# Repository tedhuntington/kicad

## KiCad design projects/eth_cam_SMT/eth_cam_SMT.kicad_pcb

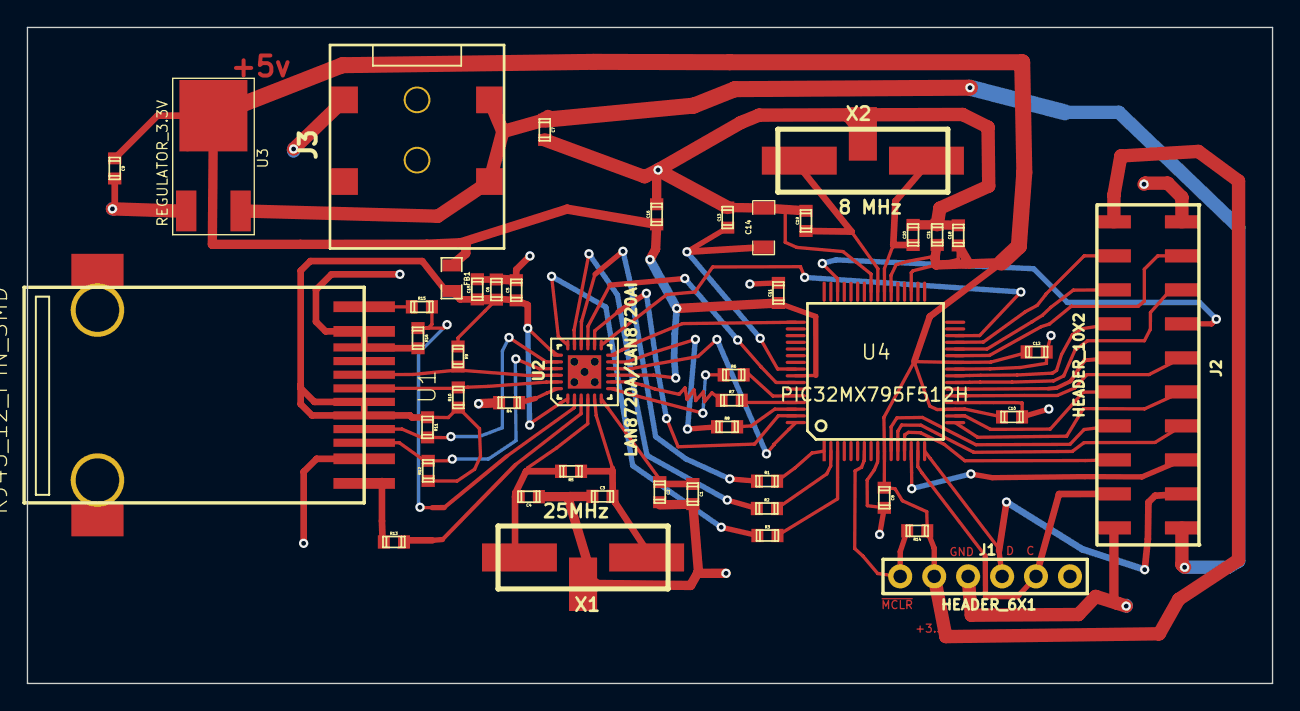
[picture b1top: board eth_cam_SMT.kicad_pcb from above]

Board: 2 copper layers, 93.0 x 49.0 mm, 46 parts (0 on the bottom side), 53 nets.

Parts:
C1, C5, C6, C8, C10, C11, C12, C13, C16, C18, C21: .1uF; TED_SM0603
C2, C15: 1uF; TED_SM0603
C3, C4, C19, C20: 18pF; TED_SM0603
C7, C9: 4.7uF; TED_SM0603
C14: 10uF; TED_SM1206
FB1: 500mA; TED_SM0805
J1: HEADER_6X1; TED_HEADER_6x1_BOTTOM
J2: HEADER_10X2; TED_HEADER_10x2_SMT
J3: Logic DC_2.1MM; TED_DC_2.1mm_SMT
R1, R2, R3, R6, R7, R8: 33; TED_SM0603
R4: 12.1k 1%; TED_SM0603
R5: 1M; TED_SM0603
R9, R10, R11, R12: 49.9; TED_SM0603
R13, R15: 249; TED_SM0603
R14: 4.7k; TED_SM0603
R16: 10k 1%; TED_SM0603
U1: RJ45_12_PIN_SMD; TED_RJ45_12pin_SMD
U2: LAN8720A/LAN8720AI; TED_QFN24
U3: REGULATOR_3.3V; TED_3v_DPAK
U4: PIC32MX795F512H; TQFP_64
X1: 25MHz; TED_crystal_W_GND_SMT_13x5mm
X2: 8 MHz; TED_crystal_W_GND_SMT_13x5mm

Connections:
+3.3v: C8.1, C9.1, C10.1, C11.1, C12.1, C16.1, C18.1, C21.1, FB1.1, J1.2, J2.11, R14.1, U2.9, U3.2, U4.10, U4.19, U4.26, U4.35, U4.38, U4.57
+5v: C7.1, J2.1, J3.1, U3.3
AVDD: C5.1, C6.1, C15.1, FB1.2, R9.1, R10.1, R11.1, R12.1, U1.5, U1.6, U2.1, U2.19
ECRSDV: R8.2, U4.62
EMDC: U2.13, U4.30
EMDIO: U2.12, U4.49
EREFCLK: U2.14, U4.63
ERXD0: R7.2, U4.61
ERXD1: R6.2, U4.60
ERXERR: U2.10, U4.64
ETXD0: R2.2, U4.2
ETXD1: R3.2, U4.3
ETXEN: R1.2, U4.1
GND: C1.2, C2.2, C3.1, C4.1, C5.2, C6.2, C7.2, C8.2, C9.2, C10.2, C11.2, C12.2, C13.2, C14.2, C15.2, C16.2, C18.2, C19.2, C20.2, C21.2, J1.3, J2.10, J2.20, J3.2, R4.2, R16.2, U1.2, U1.10, U1.11, U2.25, U3.1, U4.9, U4.20, U4.25, U4.41, X1.3, X2.3
GreenLED: R15.1, U1.12
ICSPCLK_RB1: J1.5, J2.19, U4.15
ICSPDAT_RB0: J1.4, J2.2, U4.16
unnamed: R7.1, U2.8
unnamed: R6.1, U2.7
unnamed: R4.1, U2.24
unnamed: R13.2, U2.3
unnamed: R15.2, R16.1, U2.2
unnamed: C19.1, U4.40, X2.1
unnamed: R1.1, U2.16
unnamed: R2.1, U2.17
unnamed: R3.1, U2.18
unnamed: C4.2, R5.2, U2.4, X1.2
unnamed: C3.2, R5.1, U2.5, X1.1
unnamed: C1.1, C2.1, U2.6
unnamed: R8.1, U2.11
unnamed: C13.1, C14.1, U4.56
unnamed: C20.1, U4.39, X2.2
RB2: J2.3, U4.14
RB3: J2.18, U4.13
RB4: J2.4, U4.12
RB5: J2.17, U4.11
RB6: J2.5, U4.17
RB7: J2.16, U4.18
RB8: J2.6, U4.21
RB9: J2.15, U4.22
RB10: J2.8, U4.23
RB11: J2.14, U4.24
RB12: J2.9, U4.27
RB13: J2.13, U4.28
RB14: J2.12, U4.29
RD0: J2.7, U4.46
RXN: R9.2, U1.8, U2.22
RXP: R10.2, U1.7, U2.23
TXN: R11.2, U1.4, U2.20
TXP: R12.2, U1.3, U2.21
YellowLED: R13.1, U1.1
nRST: U2.15, U4.58
~MCLR~: J1.1, R14.2, U4.7

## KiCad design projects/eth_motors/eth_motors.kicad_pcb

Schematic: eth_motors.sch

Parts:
C1, C6, C16: .1uF
C2, C15: 1uF
C3, C4: 18pF
C7, C9: 4.7uF
FB1: 500mA
H1, H2, H3, H4: HOLE
J1: HEADER_6X1
J3: Logic DC_2.1MM; TED_DC_2.1mm
R1, R2, R3, R6, R7, R8: 33
R4: 12.1k 1%
R5: 1M
R9, R10, R11, R12: 49.9
R13, R15: 249
R16: 10k 1%
U1: RJ45_12_PIN_SMD
U2: LAN8720A/LAN8720AI; QFN24
U3: REGULATOR
X1: 25MHz

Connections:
+2.8v: C9.1, C16.1, FB1.1, J1.2, U2.9, U3.2; also elsewhere on the board
+5v: C7.1, J3.1, U3.3
AECRSDV: R8.2; also elsewhere on the board
AEMDC: U2.13; also elsewhere on the board
AEMDIO: U2.12; also elsewhere on the board
AEREFCLK: U2.14; also elsewhere on the board
AERXD0: R7.2; also elsewhere on the board
AERXD1: R6.2; also elsewhere on the board
AERXERR: U2.10; also elsewhere on the board
AETXD0: R2.2; also elsewhere on the board
AETXD1: R3.2; also elsewhere on the board
AETXEN: R1.2; also elsewhere on the board
AVDD: C6.1, C15.1, FB1.2, R9.1, R10.1, R11.1, R12.1, U1.5 (CT), U1.6 (CT), U2.1, U2.19
GND: C1.2, C2.2, C3.1, C4.1, C6.2, C7.2, C9.2, C15.2, C16.2, J1.3, J3.2, R4.2, R16.2, U1.2 (YellowLED-), U1.10 (CHS_GROUND), U1.11 (GreenLED-), U2.25, U3.1; also elsewhere on the board
GreenLED: R15.1, U1.12 (GreenLED+)
ICSPCLK_RB1: J1.5; also elsewhere on the board
ICSPDAT_RB0: J1.4; also elsewhere on the board
unnamed: R15.2, R16.1, U2.2
unnamed: R13.2, U2.3
unnamed: R4.1, U2.24
unnamed: R6.1, U2.7
unnamed: R7.1, U2.8
unnamed: C3.2, R5.1, U2.5, X1.1
unnamed: R1.1, U2.16
unnamed: R2.1, U2.17
unnamed: R3.1, U2.18
unnamed: R8.1, U2.11
unnamed: C4.2, R5.2, U2.4, X1.2
unnamed: C1.1, C2.1, U2.6
RXN: R9.2, U1.8 (RD-), U2.22
RXP: R10.2, U1.7 (RD+), U2.23
TXN: R11.2, U1.4 (TD-), U2.20
TXP: R12.2, U1.3 (TD+), U2.21
YellowLED: R13.1, U1.1 (YellowLED+)
nRST: U2.15; also elsewhere on the board
~MCLR~: J1.1; also elsewhere on the board

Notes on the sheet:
Ethernet = 100Mbps (10ns/bit), SPI = 25Mbps (40ns/bit), I2C (1 Mbaud/400khz clk)
ICSP Header 90 degree thru-hole (on bottom)
PCB uses all SMT except ICD header
Note: With Ethernet, only two SPI buses are possible (SPI2 and SPI4)
Yellow=Link/Action
Green=Bus Speed 100Mbit=lit
todo: change 2.8v to VDD

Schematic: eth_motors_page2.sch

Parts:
C8, C10, C11, C12, C13, C14, C18, C21, C22: .1uF
C17: 10uF
C19, C20: 18pF
R14: 4.7k
U4: PIC32MX675F512L_TQFP
X2: 8MHz

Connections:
+2.8v: C8.1, C10.1, C11.1, C12.1, C13.1, C18.1, C21.1, C22.1, R14.1, U4.2 (VDD), U4.16 (VDD), U4.30 (AVDD), U4.37 (VDD), U4.46 (VDD), U4.55 (VUSB3V3), U4.62 (VDD), U4.86 (VDD); also elsewhere on the board
AECRSDV: U4.12 (ERXDV/AERXDV/ECRSDV/AECRSDV/SCL4/SDO2/U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); also elsewhere on the board
AEMDC: U4.71 (EMDC/AEMDC/IC4/PMCS1/PMA14/RD11); also elsewhere on the board
AEMDIO: U4.68 (RTCC/EMDIO/AEMDIO/IC1/RD8); also elsewhere on the board
AEREFCLK: U4.14 (ERXCLK/AERXCLK/EREFCLK/AEREFCLK/~SS2~/U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); also elsewhere on the board
AERXD0: U4.18 (AERXD0/INT1/RE8); also elsewhere on the board
AERXD1: U4.19 (AERXD1/INT2/RE9); also elsewhere on the board
AERXERR: U4.1 (AERXERR/RG15); also elsewhere on the board
AETXD0: U4.47 (AETXD0/~SS3~/U4RX/~U1CTS~/CN20/RD14); also elsewhere on the board
AETXD1: U4.48 (AETXD1/SCK3/U4TX/U1RTS/CN21/RD15); also elsewhere on the board
AETXEN: U4.67 (AETXEN/SDA1/IN4/RA15); also elsewhere on the board
GND: C8.2, C10.2, C11.2, C12.2, C13.2, C14.2, C17.2, C18.2, C19.2, C20.2, C21.2, C22.2, U4.15 (VSS), U4.31 (AVSS), U4.36 (VSS), U4.45 (VSS), U4.65 (VSS), U4.75 (VSS); also elsewhere on the board
ICSPCLK_RB1: U4.24 (PGEC1/AN1/CN3/RB1); also elsewhere on the board
ICSPDAT_RB0: U4.25 (PGED1/AN0/CN2/RB0); also elsewhere on the board
unnamed: C19.1, U4.64 (OSC2/CLKO/RC15), X2.1
unnamed: C14.1, C17.1, U4.85 (VCAP/VDDCORE)
unnamed: C20.1, U4.63 (OSC1/CLKI/RC12), X2.2
RA1: U4.38 (TCK/RA1); also elsewhere on the board
RA2: U4.58 (SCL2/RA2); also elsewhere on the board
RA3: U4.59 (SDA2/RA3); also elsewhere on the board
RA4: U4.60 (TDI/RA4); also elsewhere on the board
RA5: U4.61 (TDO/RA5); also elsewhere on the board
RA6: U4.91 (TRCLK/RA6); also elsewhere on the board
RA7: U4.92 (TRD3/RA7); also elsewhere on the board
RA14: U4.66 (AETXCLK/SCL1/INT3/RA14); also elsewhere on the board
RB2: U4.23 (AN2/C2IN-/CN4/RB2); also elsewhere on the board
RB3: U4.22 (AN3/C2IN+/CN5/RB3); also elsewhere on the board
RB4: U4.21 (AN4/C1IN-/CN6/RB4); also elsewhere on the board
RB5: U4.20 (AN5/C1IN+/VBUSON/CN7/RB5); also elsewhere on the board
RB6: U4.26 (PGEC2/AN6/OCFA/RB6); also elsewhere on the board
RB7: U4.27 (PGED2/AN7/RB7); also elsewhere on the board
RB8: U4.32 (AN8/C1OUT/RB8); also elsewhere on the board
RB9: U4.33 (AN9/C2OUT/RB9); also elsewhere on the board
RB10: U4.34 (AN10/CVREFOUT/PMA13/RB10); also elsewhere on the board
RB11: U4.35 (AN11/ERXERR/AETXERR/PMA12/RB11); also elsewhere on the board
RB12: U4.41 (AN12/ERXD0/AECRS/PMA11/RB12); also elsewhere on the board
RB13: U4.42 (AN13/ERXD1/AECOL/PMA10/RB13); also elsewhere on the board
RB14: U4.43 (AN14/ERXD2/AETXD3/PMALH/PMA1/RB14); also elsewhere on the board
RB15: U4.44 (AN15/ERXD3/AETXD2/OCFB/PMALL/PMA0/CN12/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); also elsewhere on the board
RC1: U4.6 (T2CK/RC1); also elsewhere on the board
RC2: U4.7 (T3CK/RC2); also elsewhere on the board
RC3: U4.8 (T4CK/RC3); also elsewhere on the board
RC4: U4.9 (T5CK/SDI1/RC4); also elsewhere on the board
RD0: U4.72 (SDO1/OC1/INT0/RD0); also elsewhere on the board
RD1: U4.76 (OC2/RD1); also elsewhere on the board
RD2: U4.77 (OC3/RD2); also elsewhere on the board
RD3: U4.78 (OC4/RD3); also elsewhere on the board
RD4: U4.81 (OC5/PMWR/CN13/RD4); also elsewhere on the board
RD5: U4.82 (PMRD/CN14/RD5); also elsewhere on the board
RD6: U4.83 (ETXEN/PMD14/CN15/RD6); also elsewhere on the board
RD7: U4.84 (ETXCLK/PMD15/CN16/RD7); also elsewhere on the board
RD9: U4.69 (~SS1~/IC2/RD9); also elsewhere on the board
RD10: U4.70 (SCK1/IC3/PMCS2/PMA15/RD10); also elsewhere on the board
RD12: U4.79 (ETXD2/IC5/PMD12/RD12); also elsewhere on the board
RD13: U4.80 (ETXD3/PMD13/CN19/RD13); also elsewhere on the board
RE0: U4.93 (PMD0/RE0); also elsewhere on the board
RE1: U4.94 (PMD1/RE1); also elsewhere on the board
RE2: U4.98 (PMD2/RE2); also elsewhere on the board
RE3: U4.99 (PMD3/RE3); also elsewhere on the board
RE4: U4.100 (PMD4/RE4); also elsewhere on the board
RE5: U4.3 (PMD5/RE5); also elsewhere on the board
RE6: U4.4 (PMD6/RE6); also elsewhere on the board
RE7: U4.5 (PMD7/RE7); also elsewhere on the board
RF0: U4.87 (EXTD1/PMD11/RF0); also elsewhere on the board
RF1: U4.88 (ETXD0/PMD10/RF1); also elsewhere on the board
RF3: U4.51 (USBID/RF3); also elsewhere on the board
RF4: U4.49 (SDA5/SDI4/U2RX/PMA9/CN17/RF4); also elsewhere on the board
RF5: U4.50 (SCL5/SDO4/U2TX/PMA8/CN18/RF5); also elsewhere on the board
RF12: U4.40 (~SS4~/U5RX/U2CTS/RF12); also elsewhere on the board
RF13: U4.39 (SCK4/U5TX/~U2RTS~/RF13); also elsewhere on the board
RG0: U4.90 (PMD8/RG0); also elsewhere on the board
RG1: U4.89 (ETXERR/PMD9/RG1); also elsewhere on the board
RG2: U4.57 (D+/RG2); also elsewhere on the board
RG3: U4.56 (D-/RG3); also elsewhere on the board
RG6: U4.10 (ECOL/SCK2/U6TX/~U3RTS~/PMA5/CN8/RG6); also elsewhere on the board
RG7: U4.11 (ECRS/SDA4/SDI2/U3RX/PMA4/CN9/RG7); also elsewhere on the board
RG12: U4.96 (TRD1/RG12); also elsewhere on the board
RG13: U4.97 (TRD0/RG13); also elsewhere on the board
RG14: U4.95 (TRD2/RG14); also elsewhere on the board
nRST: U4.17 (TMS/RA0); also elsewhere on the board
~MCLR~: R14.2, U4.13 (~MCLR~); also elsewhere on the board

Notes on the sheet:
note: later may want to add secondary clock (32.768 khz) to save power when not in use
VUSB3V3: USB internal transceiver supply. If the USB module is not used, this pin must be connected to VDD.
Note: This PIC requires 3.3V to program

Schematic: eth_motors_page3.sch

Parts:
J2, J4, J5, J6, J7, J8, J9, J10, J11, J12, J13, J14, J15, J16, J17, J18: HEADER_3X2

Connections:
+2.8v: J2.1, J4.1, J5.1, J6.1, J7.1, J8.1, J9.1, J10.1, J11.1, J12.1, J13.4, J14.4, J15.4, J16.4, J17.4, J18.4; also elsewhere on the board
GND: J2.6, J4.6, J5.6, J6.6, J7.6, J8.6, J9.6, J10.6, J11.6, J12.6, J13.3, J14.3, J15.3, J16.3, J17.3, J18.3; also elsewhere on the board
ICSPCLK_RB1: J7.4; also elsewhere on the board
ICSPDAT_RB0: J8.4; also elsewhere on the board
RA1: J18.6; also elsewhere on the board
RA2: J16.2; also elsewhere on the board
RA3: J15.6; also elsewhere on the board
RA4: J15.5; also elsewhere on the board
RA5: J15.2; also elsewhere on the board
RA6: J9.5; also elsewhere on the board
RA7: J8.3; also elsewhere on the board
RA14: J14.6; also elsewhere on the board
RB2: J6.4; also elsewhere on the board
RB3: J5.4; also elsewhere on the board
RB4: J4.4; also elsewhere on the board
RB5: J2.4; also elsewhere on the board
RB6: J18.1; also elsewhere on the board
RB7: J17.1; also elsewhere on the board
RB8: J16.1; also elsewhere on the board
RB9: J15.1; also elsewhere on the board
RB10: J14.1; also elsewhere on the board
RB11: J13.1; also elsewhere on the board
RB12: J12.4; also elsewhere on the board
RB13: J11.4; also elsewhere on the board
RB14: J10.4; also elsewhere on the board
RB15: J9.4; also elsewhere on the board
RC1: J4.3; also elsewhere on the board
RC2: J4.2; also elsewhere on the board
RC3: J4.5; also elsewhere on the board
RC4: J2.3; also elsewhere on the board
RD0: J13.6; also elsewhere on the board
RD1: J13.5; also elsewhere on the board
RD2: J13.2; also elsewhere on the board
RD3: J12.3; also elsewhere on the board
RD4: J11.3; also elsewhere on the board
RD5: J11.2; also elsewhere on the board
RD6: J11.5; also elsewhere on the board
RD7: J10.3; also elsewhere on the board
RD9: J14.5; also elsewhere on the board
RD10: J14.2; also elsewhere on the board
RD12: J12.2; also elsewhere on the board
RD13: J12.5; also elsewhere on the board
RE0: J8.2; also elsewhere on the board
RE1: J8.5; also elsewhere on the board
RE2: J6.3; also elsewhere on the board
RE3: J6.2; also elsewhere on the board
RE4: J6.5; also elsewhere on the board
RE5: J5.3; also elsewhere on the board
RE6: J5.2; also elsewhere on the board
RE7: J5.5; also elsewhere on the board
RF0: J10.2; also elsewhere on the board
RF1: J10.5; also elsewhere on the board
RF3: J17.2; also elsewhere on the board
RF4: J17.6; also elsewhere on the board
RF5: J17.5; also elsewhere on the board
RF12: J18.2; also elsewhere on the board
RF13: J18.5; also elsewhere on the board
RG0: J9.2; also elsewhere on the board
RG1: J9.3; also elsewhere on the board
RG2: J16.5; also elsewhere on the board
RG3: J16.6; also elsewhere on the board
RG6: J2.2; also elsewhere on the board
RG7: J2.5; also elsewhere on the board
RG12: J7.2; also elsewhere on the board
RG13: J7.5; also elsewhere on the board
RG14: J7.3; also elsewhere on the board

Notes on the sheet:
Motor Controller 2
Motor Controller 15
Motor Controller 3
Motor Controller 10
Currently unused: F2, F8, RA9, RA10
Motor Controller 1
Note that: pin numbering is header-kind (not IDC)
Note that bottom 6 headers have reversed wiring because cables point in opposite direction from above

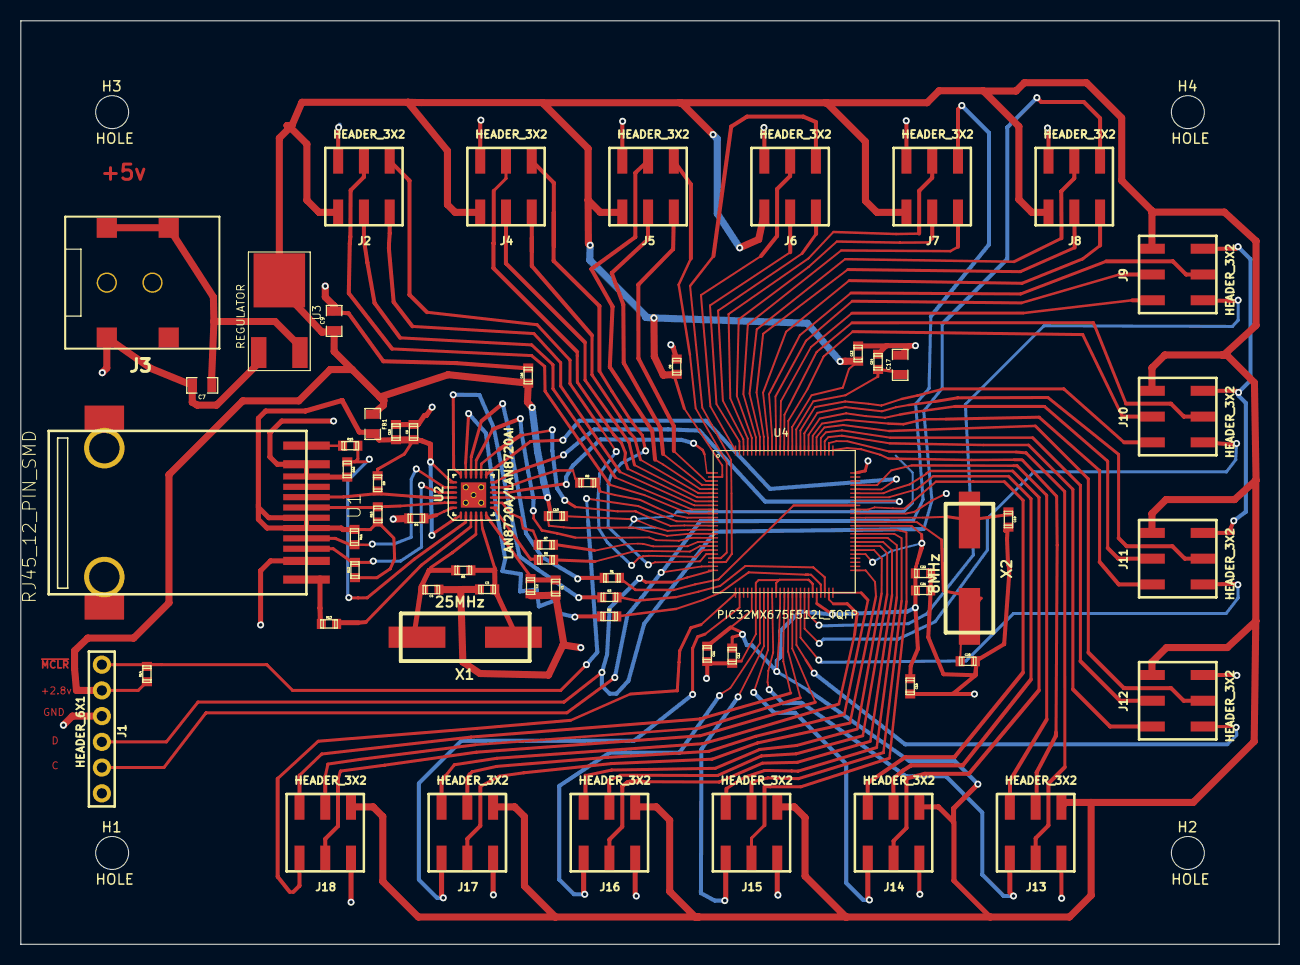
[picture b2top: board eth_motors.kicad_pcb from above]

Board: 2 copper layers, 124.0 x 91.0 mm, 66 parts (0 on the bottom side), 101 nets.
